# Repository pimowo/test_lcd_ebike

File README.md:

# e-Bike System by PMW

## Przegląd
e-Bike System by PMW to zaawansowany system zaprojektowany dla rowerów elektrycznych. Oferuje funkcje takie jak monitorowanie prędkości, pomiar temperatury, zarządzanie baterią, pomiar mocy i wiele innych. System wykorzystuje różne czujniki i komponenty, aby dostarczać dane w czasie rzeczywistym oraz opcje sterowania, które poprawiają doświadczenie jazdy na rowerze elektrycznym.

## Funkcje
- **Monitorowanie prędkości**: Wyświetla aktualną, średnią i maksymalną prędkość.
- **Pomiar temperatury**: Monitoruje temperaturę powietrza, kontrolera i silnika.
- **Obliczanie zasięgu**: Wyświetla szacowany zasięg, przebyty dystans i wartość licznika kilometrów.
- **Zarządzanie baterią**: Pokazuje napięcie, prąd, pojemność i procent naładowania baterii.
- **Pomiar mocy**: Wyświetla aktualną, średnią i maksymalną moc wyjściową.
- **Monitorowanie ciśnienia**: Monitoruje ciśnienie w oponach, napięcie i temperaturę.
- **Sterowanie USB**: Kontroluje port ładowania USB.
- **Sterowanie światłami**: Zarządza przednimi i tylnymi światłami z trybami dziennym i nocnym.
- **Interfejs użytkownika**: Interaktywny wyświetlacz OLED z wieloma ekranami i pod-ekranami dla szczegółowych informacji.

## Komponenty
- **Mikrokontroler**: ESP32
- **Wyświetlacz**: SSD1306 128x64 OLED
- **Czujnik temperatury**: DS18B20
- **Zegar czasu rzeczywistego (RTC)**: DS3231
- **Bluetooth**: BLE do komunikacji z systemem zarządzania baterią (BMS)
- **EEPROM**: Do przechowywania ustawień użytkownika

## Definicje pinów
- **Przyciski**:
  - `BTN_UP`: GPIO 13
  - `BTN_DOWN`: GPIO 14
  - `BTN_SET`: GPIO 12
- **Światła**:
  - `FrontDayPin`: GPIO 5
  - `FrontPin`: GPIO 18
  - `RealPin`: GPIO 19
- **Ładowarka USB**:
  - `UsbPin`: GPIO 32
- **Czujnik temperatury**:
  - `ONE_WIRE_BUS`: GPIO 15

## Użytkowanie
1. **Instalacja**:
    - Podłącz wszystkie komponenty zgodnie z definicjami pinów.
    - Wgraj dostarczony kod do mikrokontrolera ESP32.

2. **Obsługa**:
    - Użyj przycisku `BTN_SET` do nawigacji między głównymi ekranami.
    - Użyj przycisków `BTN_UP` i `BTN_DOWN` do zmiany ustawień lub przełączania między pod-ekranami.
    - Długie naciśnięcie `BTN_SET` włącza/wyłącza wyświetlacz.
    - Podwójne kliknięcie `BTN_SET` przełącza wyjście USB lub wchodzi do pod-ekranów.

3. **Konfiguracja**:
    - Ustawienia systemu, takie jak obwód koła i pojemność baterii, są przechowywane w EEPROM.
    - Wyświetlacz pokazuje różne ekrany dotyczące prędkości, temperatury, zasięgu, baterii, mocy i ciśnienia.

## Struktura kodu
- **Biblioteki**:
  - `Wire.h`, `U8g2lib.h`, `RTClib.h`, `OneWire.h`, `DallasTemperature.h`, `EEPROM.h`, `BLEDevice.h`, `BLEClient.h`, `BLEUtils.h`, `BLEServer.h`
- **Główny kod**:
  - `setup()`: Inicjalizuje komponenty i ustawienia.
  - `loop()`: Obsługuje wejścia przycisków, aktualizuje wyświetlacz i przetwarza dane z czujników.
- **Funkcje**:
  - `connectToBms()`: Łączy się z systemem zarządzania baterią przez BLE.
  - `loadSettingsFromEEPROM()`: Ładuje ustawienia użytkownika z EEPROM.
  - `saveSettingsToEEPROM()`: Zapisuje ustawienia użytkownika do EEPROM.
  - `drawMainDisplay()`, `drawTopBar()`, `drawAssistLevel()`, `drawLightStatus()`, `drawValueAndUnit()`: Funkcje do aktualizacji wyświetlacza OLED.
  - `handleTemperature()`: Zarządza odczytami z czujnika temperatury.

## Licencja
Projekt jest licencjonowany na podstawie licencji MIT. Zobacz plik [LICENSE](LICENSE) dla szczegółów.

## Wkład
Wkłady są mile widziane! Proszę rozwidlić repozytorium i złożyć pull request na wszelkie ulepszenia lub poprawki błędów.

## Kontakt
W razie pytań lub wsparcia prosimy o kontakt na adres [Twoje Imię] pod adresem [twoj.email@przyklad.com].

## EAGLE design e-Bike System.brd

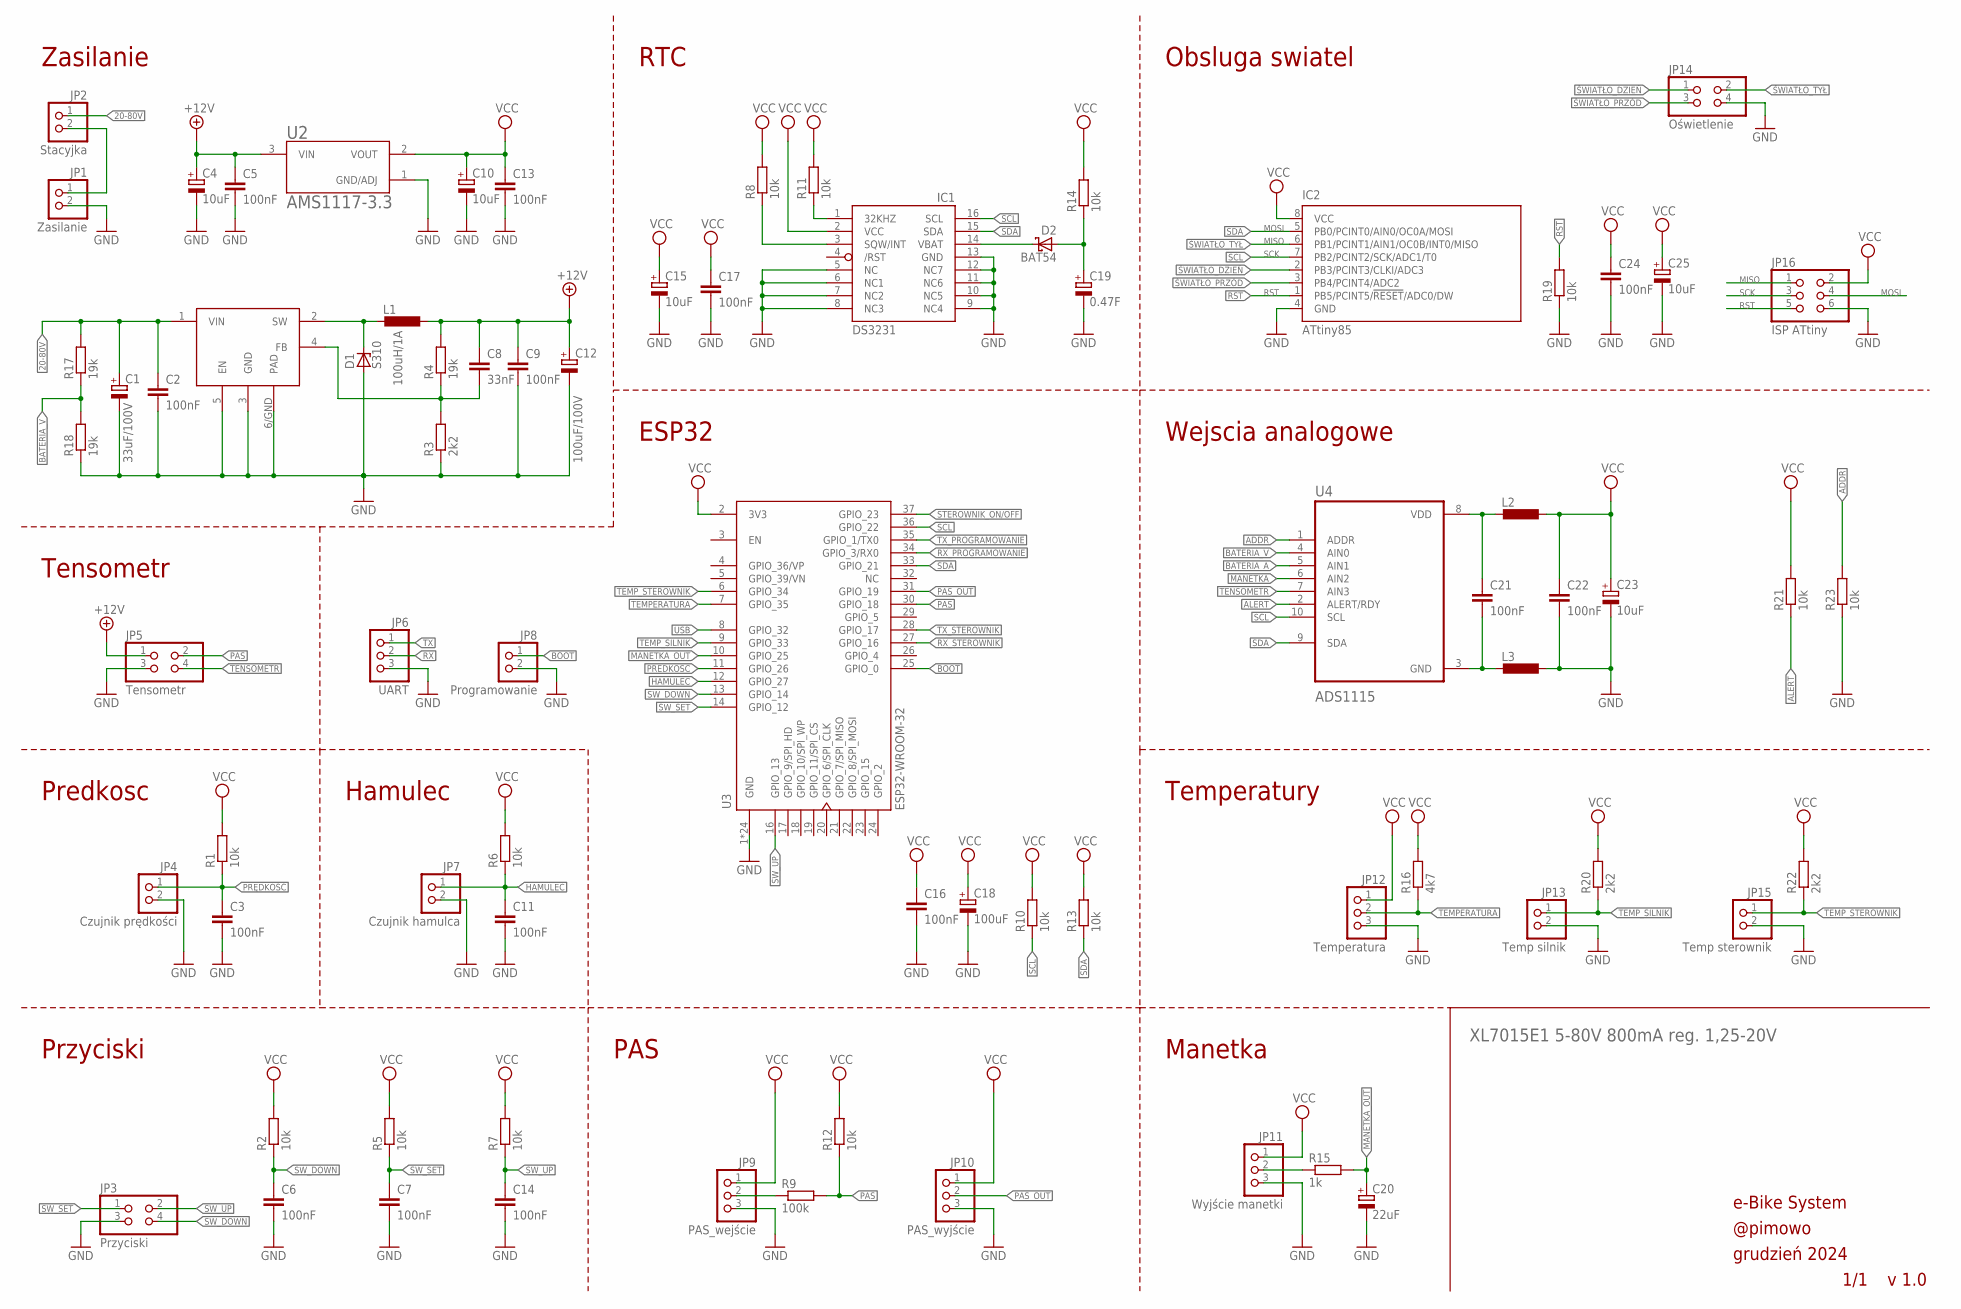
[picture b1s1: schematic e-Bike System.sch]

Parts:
C1, C12: CPOL-EUE1.8-4; E1,8-4
C2, C3, C5, C6, C7, C9, C11, C13, C14, C16, C17, C21, C22, C24: 100nF; C1206K
C4, C10, C15, C23, C25: 10uF; E1,8-4
C8: 33nF; C1206K
C18: 100uF; E1,8-4
C19: 0.47F; E7,5-16
C20: 22uF; E1,8-4
D1: S310; SMB
D2: BAT54; SOT23
IC1: DS3231/SO; SO16W
IC2: ATtiny85; 8S1
JP1: Zasilanie; 1X02
JP2: Stacyjka; 1X02
JP3: Przyciski; 2X02
JP4: Czujnik prędkości; 1X02
JP5: Tensometr; 2X02
JP6: UART; 1X03
JP7: Czujnik hamulca; 1X02
JP8: Programowanie; 1X02
JP9: PAS_wejście; 1X03
JP10: PAS_wyjście; 1X03
JP11: Wyjście manetki; 1X03
JP12: Temperatura; 1X03
JP13: Temp silnik; 1X02
JP14: Oświetlenie; 2X02
JP15: Temp sterownik; 1X02
JP16: ISP ATtiny; 2X03
L1: L-EUL5650M; L5650M
L2, L3: L-EUL1812; L1812
R1, R2, R5, R6, R7, R8, R10, R11, R12, R13, R14, R19, R21, R23: 10k; M1206
R3, R20, R22: 2k2; M1206
R4, R17, R18: 19k; M1206
R9: 100k; M1206
R15: 1k; M1206
R16: 4k7; M1206
U1: XL7015; TO-252-5L
U2: AMS1117-3.3; SOT229P700X180-4N
U3: ESP32-WROOM-32; MODULE_ESP32-WROOM-32
U4: ADS1115; SOP50P490X110-10N

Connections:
20-80V: C1.+, C2.1, JP2.1, R17.2, U1.1 (VIN)
+12V: C4.+, C5.1, C8.1, C9.1, C12.+, JP5.1, L1.1, R4.2, U2.3 (VIN)
ADDR: R23.2, U4.1 (ADDR)
ALERT: R21.1, U4.2 (ALERT/RDY)
BATERIA_A: U4.5 (AIN1)
BATERIA_V: R17.1, R18.2, U4.4 (AIN0)
BOOT: JP8.1, U3.25 (GPIO_0)
GND: C1.-, C2.2, C3.2, C4.-, C5.2, C6.2, C7.2, C9.2, C10.-, C11.2, C12.-, C13.2, C14.2, C15.-, C16.2, C17.2, C18.-, C19.-, C20.-, C22.2, C23.-, C24.2, C25.-, D1.A, IC1.5 (NC), IC1.6 (NC1), IC1.7 (NC2), IC1.8 (NC3), IC1.9 (NC4), IC1.10 (NC5), IC1.11 (NC6), IC1.12 (NC7), IC1.13 (GND), IC2.4 (GND), JP1.2, JP3.3, JP4.2, JP5.3, JP6.3, JP7.2, JP8.2, JP9.3, JP10.3, JP11.3, JP12.3, JP13.2, JP14.4, JP15.2, JP16.6, L3.1, R3.1, R18.1, R19.1, R23.1, U1.3 (GND), U1.5 (EN), U1.6/GND (PAD), U2.1 (GND/ADJ), U3.1 (GND), U3.15 (GND), U3.38 (GND), U3.39_1 (GND), U3.39_2 (GND), U3.39_3 (GND), U3.39_4 (GND), U3.39_5 (GND), U3.39_6 (GND), U3.39_7 (GND), U3.39_8 (GND), U3.39_9 (GND), U3.39_10 (GND), U3.39_11 (GND), U3.39_12 (GND), U3.39_13 (GND), U3.39_14 (GND), U3.39_15 (GND), U3.39_16 (GND), U3.39_17 (GND), U3.39_18 (GND), U3.39_19 (GND), U3.39_20 (GND), U3.39_21 (GND)
HAMULEC: C11.1, JP7.1, R6.1, U3.12 (GPIO_27)
MANETKA: U4.6 (AIN2)
MANETKA_OUT: C20.+, R15.2, U3.10 (GPIO_25)
unnamed: JP11.2, R15.1
unnamed: JP9.2, R9.1
unnamed: IC1.1 (32KHZ), R11.1
unnamed: IC1.3 (SQW/INT), R8.1
unnamed: C19.+, D2.1 (A), R14.1
unnamed: D2.3 (C), IC1.14 (VBAT)
unnamed: JP1.1, JP2.2
unnamed: C21.2, L3.2, U4.3 (GND)
unnamed: C8.2, R3.2, R4.1, U1.4 (FB)
unnamed: D1.C, L1.2, U1.2 (SW)
PAS: JP5.2, R9.2, R12.1, U3.30 (GPIO_18)
PAS_OUT: JP10.2, U3.31 (GPIO_19)
PREDKOSC: U3.11 (GPIO_26)
PRĘDKOŚĆ: C3.1, JP4.1, R1.1
RST: IC2.1 (PB5/PCINT5/!RESET!/ADC0/DW), JP16.5, R19.2
RX: JP6.2
RX_PROGRAMOWANIE: U3.34 (GPIO_3/RX0)
RX_STEROWNIK: U3.27 (GPIO_16)
SCL: IC1.16 (SCL), IC2.7 (PB2/PCINT2/SCK/ADC1/T0), JP16.3, R10.1, U3.36 (GPIO_22), U4.10 (SCL)
SDA: IC1.15 (SDA), IC2.5 (PB0/PCINT0/AIN0/OC0A/MOSI), JP16.4, R13.1, U3.33 (GPIO_21), U4.9 (SDA)
STEROWNIK_ON/OFF: U3.37 (GPIO_23)
SW_DOWN: C6.1, JP3.4, R2.1, U3.13 (GPIO_14)
SW_SET: C7.1, JP3.1, R5.1, U3.14 (GPIO_12)
SW_UP: C14.1, JP3.2, R7.1, U3.16 (GPIO_13)
TEMPERATURA: JP12.2, R16.1, U3.7 (GPIO_35)
TEMP_SILNIK: JP13.1, R20.1, U3.9 (GPIO_33)
TEMP_STEROWNIK: JP15.1, R22.1, U3.6 (GPIO_34)
TENSOMETR: JP5.4, U4.7 (AIN3)
TX: JP6.1
TX_PROGRAMOWANIE: U3.35 (GPIO_1/TX0)
TX_STEROWNIK: U3.28 (GPIO_17)
USB: U3.8 (GPIO_32)
VCC: C10.+, C13.1, C15.+, C16.1, C17.1, C18.+, C22.1, C23.+, C24.1, C25.+, IC1.2 (VCC), IC2.8 (VCC), JP9.1, JP10.1, JP11.1, JP12.1, JP16.2, L2.1, R1.2, R2.2, R5.2, R6.2, R7.2, R8.2, R10.2, R11.2, R12.2, R13.2, R14.2, R16.2, R20.2, R21.2, R22.2, U2.2 (VOUT), U3.2 (3V3)
VDD: C21.1, L2.2, U4.8 (VDD)
ŚWIATŁO_DZIEŃ: IC2.2 (PB3/PCINT3/CLKI/ADC3), JP14.1
ŚWIATŁO_PRZÓD: IC2.3 (PB4/PCINT4/ADC2), JP14.3
ŚWIATŁO_TYŁ: IC2.6 (PB1/PCINT1/AIN1/OC0B/INT0/MISO), JP14.2, JP16.1

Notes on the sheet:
1/1
v 1.0
e-Bike System
@pimowo
grudzień 2024
ESP32
MOSI
MISO
SCK
RST
Obsluga swiatel
Wejscia analogowe
RTC
Przyciski
Hamulec
Predkosc
PAS
Temperatury
Manetka
Zasilanie
Tensometr
XL7015E1 5-80V 800mA reg. 1,25-20V
33uF/100V
100uF/100V
100uH/1A

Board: 2 copper layers, 75 parts (3 on the bottom side), 37 nets, no tracks yet.

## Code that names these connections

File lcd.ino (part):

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// GPIO13, GPIO14, GPIO16, GPIO17, GPIO18, GPIO19, GPIO21, GPIO22, GPIO23, GPIO25, GPIO26, GPIO27, GPIO32, GPIO33

// ===== CZUJNIKI E-BIKE =====
#define PIN_BRAKE      33    // Hamulec
#define PIN_PAS        25    // PAS (czujnik pedałowania)
#define PIN_SPEED      26    // Pomiar prędkości
#define PIN_CADENCE    27    // Pomiar kadencji
#define PIN_THROTTLE   23    // Manetka wyjście
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float pressure_rear_bar = 0;      // tylne koło
float pressure_voltage = 0;       // napięcie przedniego czujnika
float pressure_rear_voltage = 0;  // napięcie tylnego czujnika
float pressure_temp = 0;          // temperatura przedniego czujnika
float pressure_rear_temp = 0;     // temperatura tylnego czujnika

// --- Zmienne dla czujnika temperatury ---
#define TEMP_ERROR -999.0
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int assistLevel = 3;
bool assistLevelAsText = false;
int lightMode = 0;        // 0=off, 1=dzień, 2=noc
int assistMode = 0;       // 0=PAS, 1=STOP, 2=GAZ, 3=P+G
bool usbEnabled = false;  // Stan wyjścia USB

// --- Obiekty ---
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
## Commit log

2024-12-13 deep sleep lcd.ino
